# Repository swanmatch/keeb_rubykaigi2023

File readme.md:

# RubyKaigi 2023 ノベルティキーボード ビルドガイド

**[English page is Here](./readme_en.md)**

## 概要

RubyKaigi 2023で配布するマイクロパッド。  
小さいながらもアングルドタクトスイッチを搭載することで合計8キーを搭載可能。  
とても小さくはんだ付け箇所も少ないので、初めての電子工作、ファームウェアにいいかもしれない。  
アンダーグローとバックライトを両方採用しているので、**とても良く光ります。**

## 部品

### 付属品

| 品目                    | 数量 |
| :---------------------- | ---: |
| PCB                     |  1枚 |
| ボトムプレート          |  1枚 |
| LED小(SK6812mini)       |  4個 |
| LED大(WS2812B)          |  1個 |
| M2L7丸スペーサ          |  3本 |
| M2L4ネジ                |  6本 |
| タクトスイッチ(大)      |  4個 |
| ゴム足                  |  4個 |

### 別途必要なもの

| 品目                     | 数量 | 入手先 |
| :----------------------- | ---: | :----- |
| XIAO RP2040              |  1個 | [talpkeyboard](https://talpkeyboard.net/items/63534f58f5197322fceb6487)<br>[秋月電子](https://akizukidenshi.com/catalog/g/gM-17044/) |
| 7ピン ピンヘッダ(*1)     |  2本 | [遊舎工房](https://shop.yushakobo.jp/products/3696?_pos=2&_sid=62c590295&_ss=r&variant=42476836946151)<br>[秋月電子](https://akizukidenshi.com/catalog/g/gC-00167/) |
| MX互換スイッチ(5pin推奨) |  4個 | [遊舎工房](https://shop.yushakobo.jp/collections/all-switches)<br>[talpkeyboard](https://talpkeyboard.net/?category_id=59cf8860ed05e668db003f5d) |
| 1Uキーキャップ           |  4個 | [遊舎工房](https://shop.yushakobo.jp/collections/keycaps/products/dsa-blank-keycaps)<br>[talpkeyboard](https://talpkeyboard.net/?category_id=59e2acfaed05e644fd004008) |
| USBケーブル(TYPE-C)      |  1本 | 100円ショップなど |

*1 ) XIAO RP2040は販売元によってピンヘッダが付属している場合もあるので注意してください。  
折って使えるタイプのものであれば14ピン以上のものを1つ購入して7ピンずつに折ればよいです。  
プロマイクロに付属しているピンヘッダが余っていればそれも使えます。

## 工具

| 品目               | 入手先 |
| :----------------- | :----- |
| 温度調整ハンダゴテ | [Amazon](https://www.amazon.co.jp/gp/product/B08L6KJBGP/ref=as_li_tl?ie=UTF8&camp=247&creative=1211&creativeASIN=B08L6KJBGP&linkCode=as2&tag=swanmatch06-22&linkId=902f31009670f3b7cd79891d00479e72)、ホームセンターなど |
| 低温はんだ         | 100円ショップなど |
| ピンセット         | 100円ショップなど |
| マスキングテープ   | 100円ショップなど |
| ニッパー           | 100円ショップなど |
| テスター (トラブル時に必要) | [Amazon](https://www.amazon.co.jp/gp/product/B07GJ891VR/ref=as_li_tl?ie=UTF8&camp=247&creative=1211&creativeASIN=B07GJ891VR&linkCode=as2&tag=swanmatch06-22&linkId=bd42afeb7ff9ca4a61af44a62215c148)、ホームセンターなど |

## 組み立て手順

### ファームウェア

実装を始める前に、まずはRP2040マイコンが正常に機能しているか確認してください。

1. XIAO RP2040のBootボタン(向かって右側のボタン)を押しながらUSBケーブルでPCと接続して、`RPI-RP2`というボリュームのファイルシステムとしてマウントされることを確認してください。
2. [PRK Firmware](https://github.com/picoruby/prk_firmware/releases)から.u2fファイルをダウンロードします。(特にこだわりなければ最新の安定版)
3. マウントされたRP2040のファイルシステムにu2fファイルをドラッグ&ドロップします。
4. `PRK_FIRMWARE`として再マウントされるので、[keymap.rb](./keymap.rb)をダウンロードしてドラッグ&ドロップしてください。

この手順がうまく行かない場合RP2040の初期不良である可能性が高いです。  
運が悪かったと諦めてもう一つ購入してください...

### SK6812MINI

LED(小)をはんだ付けします。  
三角のシルクマークが付いているパッドがLEDの欠けているタブに対応しています。  

LEDは比較的熱に弱いので、温度調整はんだごてで240℃くらいで、手早くはんだ付けしてください。

### WS2812B

LED(大)をはんだ付けします。

左上(┌)がLEDのかけている角に対応しています。

まず一箇所のパッドにハンダを盛ります。

次にそのパッドを温めながらピンセットでLEDをパッドの上に乗せて、位置が決まったらコテを離してハンダを冷やして固めます。(難しいところ)

残りのパッドにハンダを流し込みます。

### ピンヘッダ

**このあたりから手順を間違えると結構リカバリが面倒なので注意し作業を行ってください。**

ピンヘッダを基板に差し込みます。

RP2040を差し込みます。**(RP2040のはんだ付けはまだしないこと！)**

マスキングテープで仮止めします。  
(仮止めできればなんでもいいのですが、セロハンテープは熱で溶けそうなのであまりよくないと思います。)

ある程度きちんと固定しておかないと、ピンヘッダが基板に対して垂直にならず、
最悪あとでRP2040がはまらない悲しいことになります。

反対側にひっくり返します。

ピンヘッダの四隅をはんだ付けします。

すべてのピンをはんだ付けしてしまうとリカバリが困難なので、
この段階でピンヘッダが基板から浮いたりしていないかよく確認しておくといいです。

問題なければすべてのピンをはんだ付けしてください。

### スイッチ

基板をひっくり返してスイッチをはめ込みます。

5pinは位置がブレるのを防ぐためにあえて固めにしているので、強く奥まで押し込んでください。

3pinタイプのスイッチの場合はスイッチが微妙に傾いてしまって、キーキャップが干渉してしまうことがあるのであんまりオススメしないです。  

再度裏面にひっくり返して、スイッチをはんだ付けします。  

### タクトスイッチ

タクトスイッチを裏面から差し込みます。

反対側(表、スイッチ側)に戻してはんだ付けします。

タクトスイッチのピンが表面にあるので、余分な分はニッパーで切っておくといいです。

はんだ付け面が表に来るのが気になる方はタクトスイッチを表面に実装しても回路的には問題ありませんが、
取り付けるスイッチやキーキャップによってはキーキャップがタクトスイッチに干渉してしまう場合があります。

### RP2040

部品実装面が上になるようにRP2040を乗せます。  

ピンヘッダがちょっと長いのでニッパーで切り落とします。  
↓が長さの目安です。

はんだ付けします。

### ボトムプレート、ゴム足

回路基板とボトムプレートをスペーサーでネジ止めして、ボトムプレートの四隅にゴム足を貼り付けます。  
(完成が近づくにつれて早る気持ちを抑えきれずに写真撮り忘れます)

## 完成

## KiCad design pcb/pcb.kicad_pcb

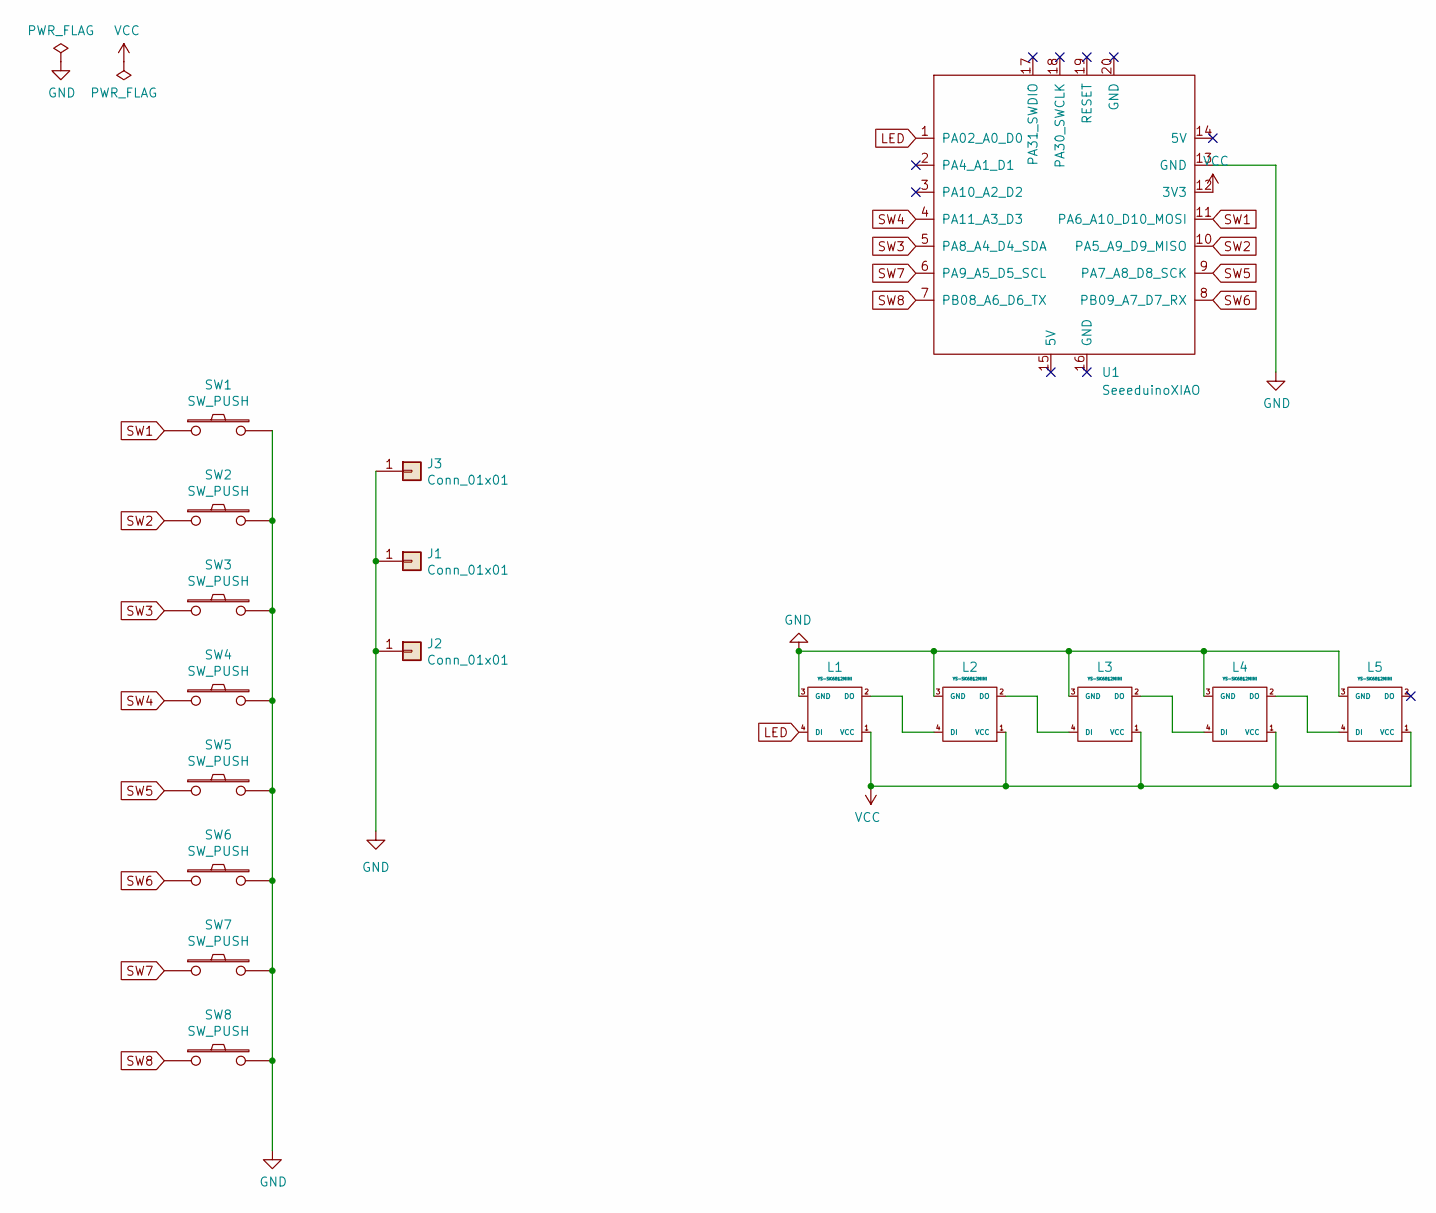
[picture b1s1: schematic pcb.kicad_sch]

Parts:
J1, J2, J3: Conn_01x01; MountingHole_2.2mm_M2_Pad_Via
L1: YS-SK6812MINI; LED_WS2812B_PLCC4_5.0x5.0mm_P3.2mm
L2, L3, L4, L5: YS-SK6812MINI; YS-SK6812MINI-E
SW1, SW4, SW5, SW8: SW_PUSH; SW_Tactile_SPST_Angled_PTS645Vx39-2LFS
SW2, SW3, SW6, SW7: SW_PUSH; MX_1U
U1: SeeeduinoXIAO; Seeeduino XIAO TH only

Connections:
GND: J1.1, J2.1, J3.1, L1.3 (GND), L2.3 (GND), L3.3 (GND), L4.3 (GND), L5.3 (GND), SW1.2, SW2.2, SW3.2, SW4.2, SW5.2, SW6.2, SW7.2, SW8.2, U1.13 (GND)
LED: L1.4 (DI), U1.1 (PA02_A0_D0)
unnamed: L1.2 (DO), L2.4 (DI)
unnamed: L2.2 (DO), L3.4 (DI)
unnamed: L3.2 (DO), L4.4 (DI)
unnamed: L4.2 (DO), L5.4 (DI)
SW1: SW1.1, U1.11 (PA6_A10_D10_MOSI)
SW2: SW2.1, U1.10 (PA5_A9_D9_MISO)
SW3: SW3.1, U1.5 (PA8_A4_D4_SDA)
SW4: SW4.1, U1.4 (PA11_A3_D3)
SW5: SW5.1, U1.9 (PA7_A8_D8_SCK)
SW6: SW6.1, U1.8 (PB09_A7_D7_RX)
SW7: SW7.1, U1.6 (PA9_A5_D5_SCL)
SW8: SW8.1, U1.7 (PB08_A6_D6_TX)
VCC: L1.1 (VCC), L2.1 (VCC), L3.1 (VCC), L4.1 (VCC), L5.1 (VCC), U1.12 (3V3)

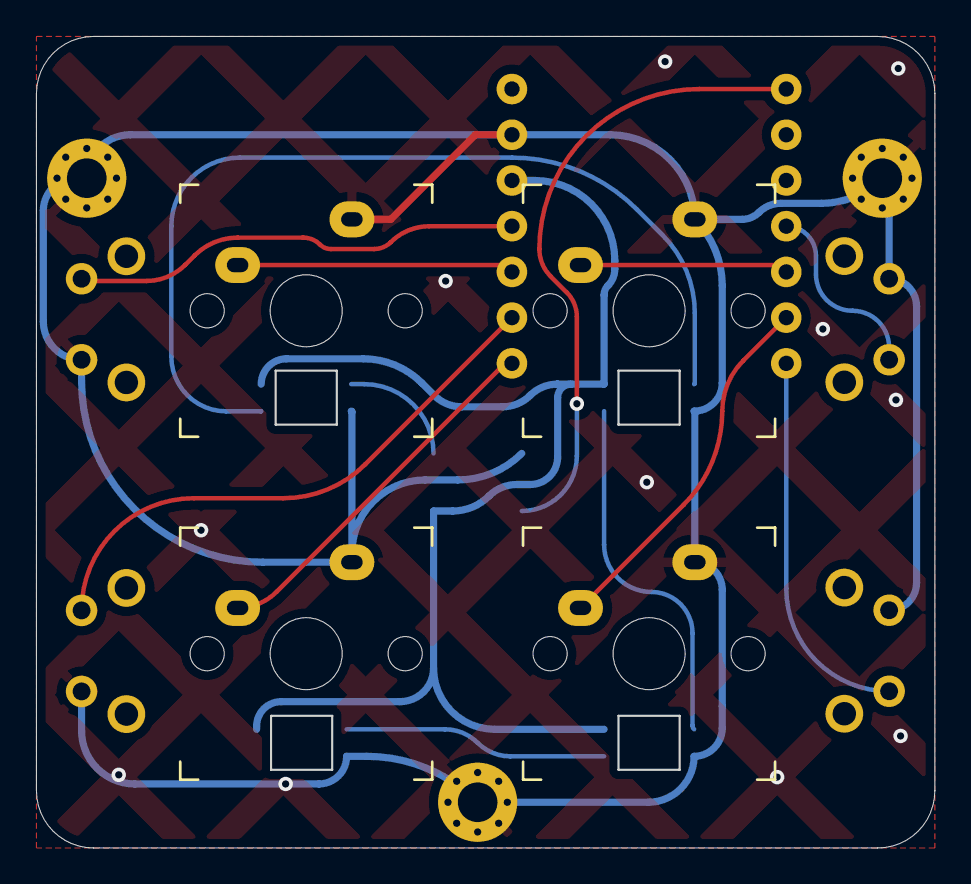
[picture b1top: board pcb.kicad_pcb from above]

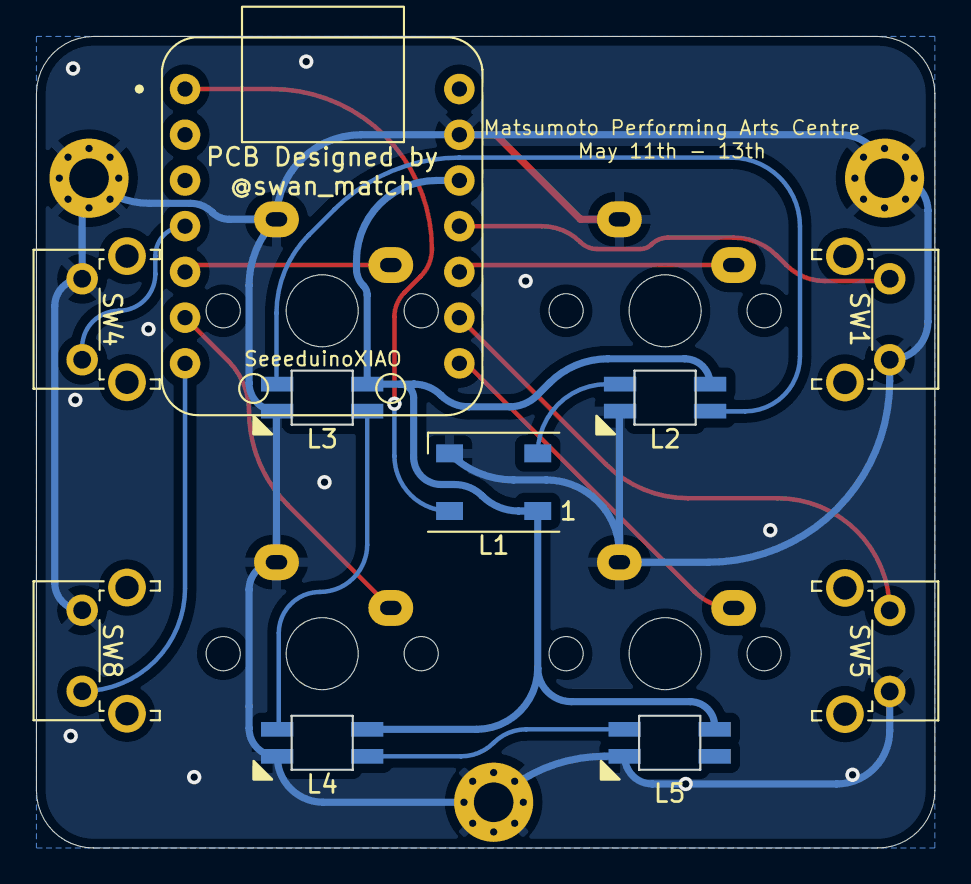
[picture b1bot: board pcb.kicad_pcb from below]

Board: 2 copper layers, 49.8 x 45.0 mm, 17 parts (10 on the bottom side), 15 nets.

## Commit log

2021-10-19 add bottom plate
2021-11-08 add via json
2021-11-10 add readme.
2021-11-10 Set theme jekyll-theme-hacker
2021-11-10 litle edit.
2021-11-10 litle edit
2021-11-11 firmware write by remap
2021-11-14 Create LICENSE
2023-02-09 create rubykaigi 2023
2023-02-12 add ignore
2023-04-21 add keymap.rb
2023-04-21 fix gnd
2023-04-22 create readme.
2023-04-23 きばん → 基板
2023-04-23 キースイッチとタクトスイッチの作業の写真の順番が違っていそう
2023-05-07 fix keymap
2023-05-07 fix readme
2023-05-07 revert keymap
2023-05-07 Translate readme_en.md via GitLocalize
2023-05-07 add english page link
2023-05-23 Update readme.md
    Fix typo
